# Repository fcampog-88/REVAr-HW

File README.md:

# REVAr-HW
Rede de monitoramento atmosférico de baixo custo (Hardware)

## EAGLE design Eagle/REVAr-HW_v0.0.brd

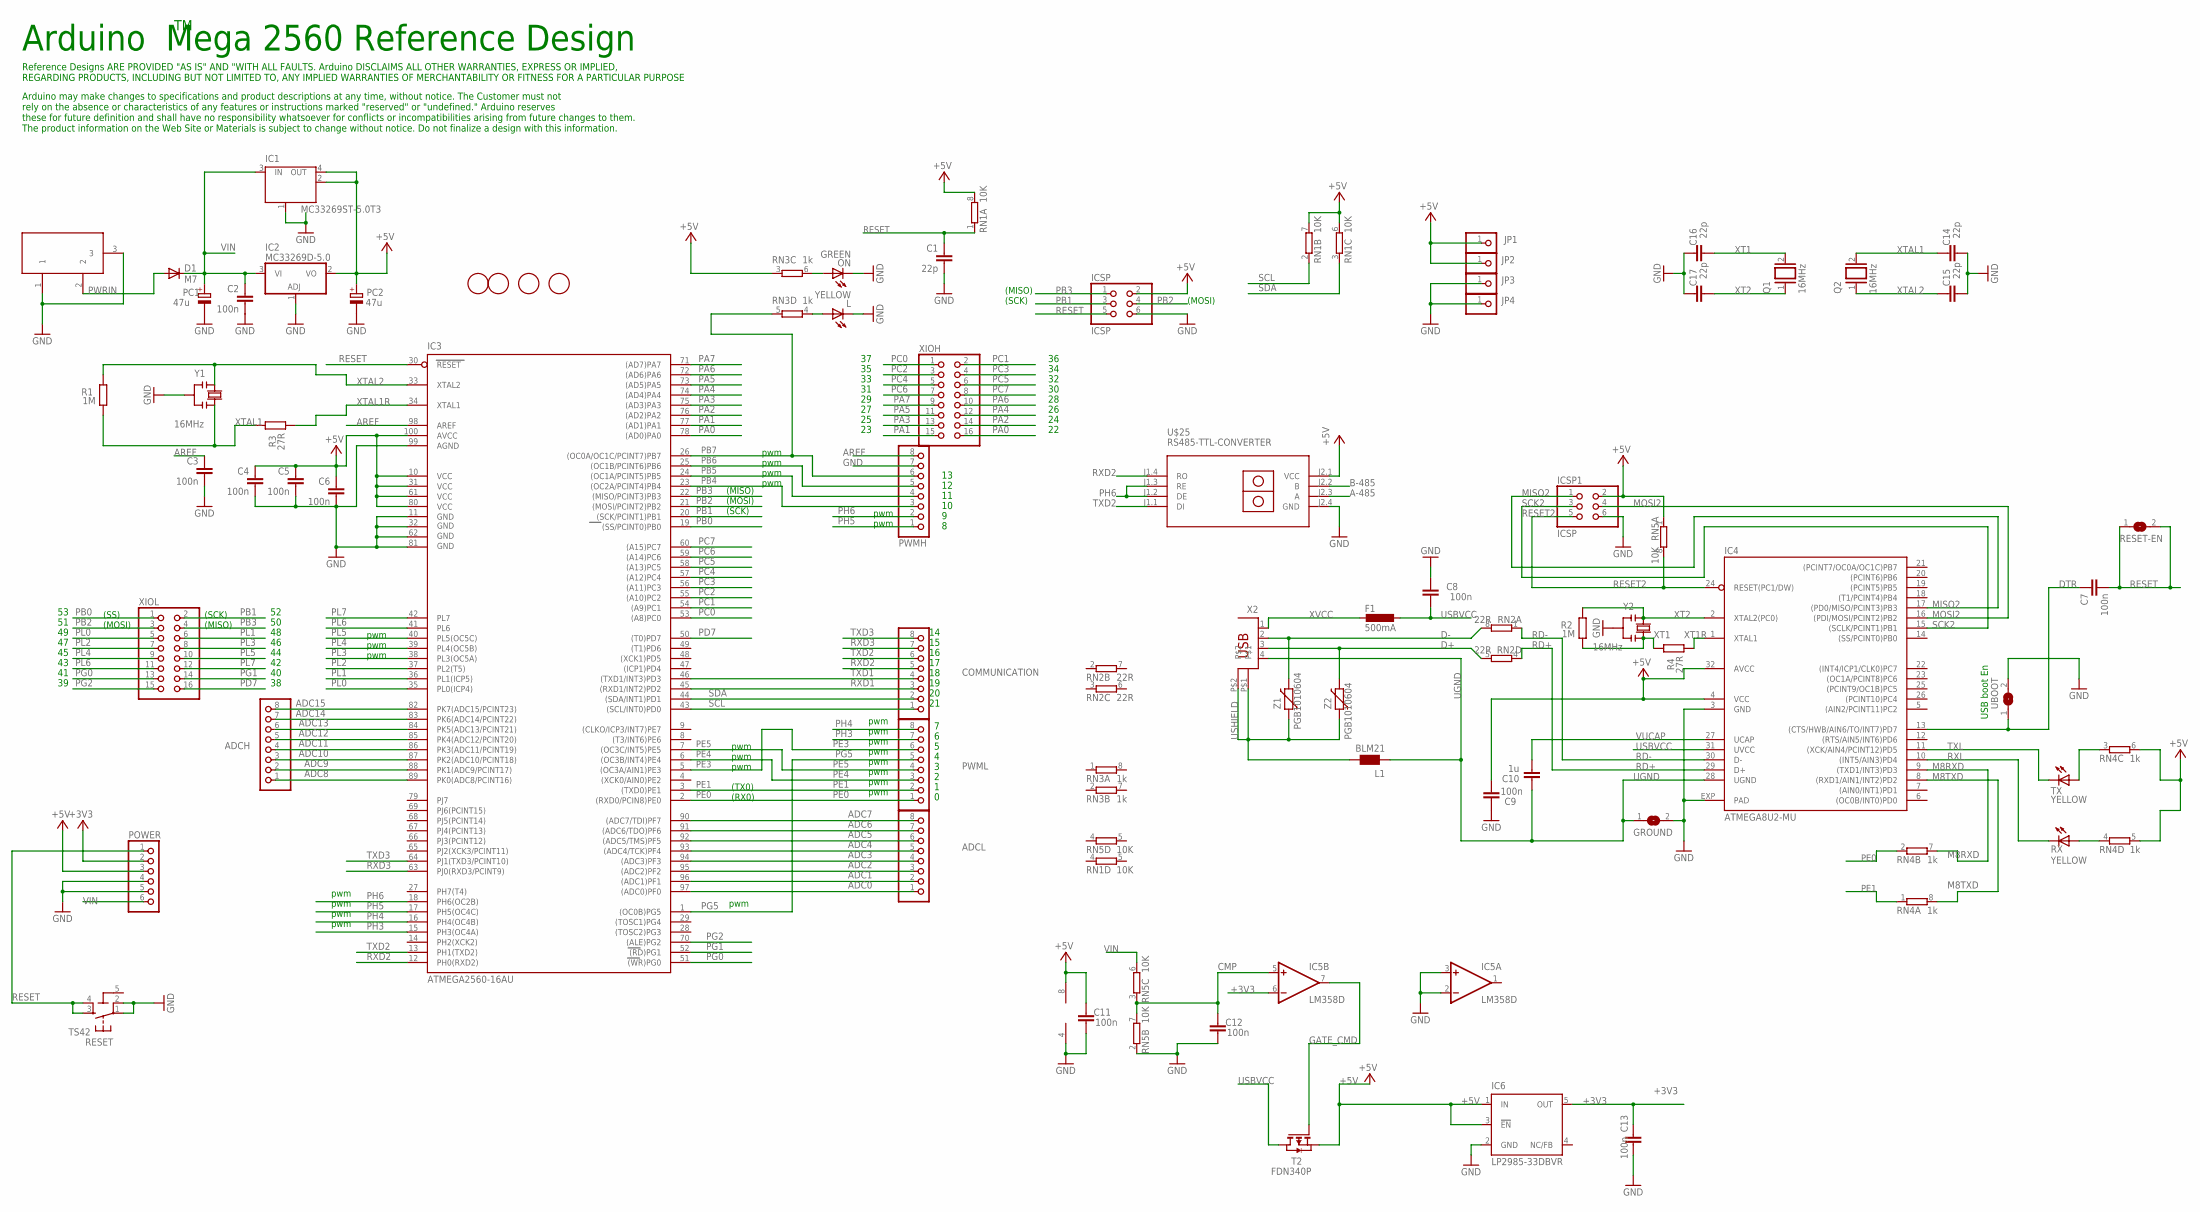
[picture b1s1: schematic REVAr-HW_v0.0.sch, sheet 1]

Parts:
ADCH: PINHD-1X8; 1X08
ADCL: PINHD-1X8; 1X08
C1, C14, C15, C16, C17: 22p; C0603-ROUND
C2, C3, C4, C5, C6, C7, C9, C12, C13: 100n; C0603-ROUND
C8, C11: 100n; C0603
C10: 1u; C0603-ROUND
COMMUNICATION: PINHD-1X8; 1X08
D1: M7; SMB
F1: 500mA; L1812
GROUND: SJ
IC1: MC33269ST-5.0T3; SOT223
IC2: MC33269D-5.0; DPACK
IC3: ATMEGA2560-16AU; TQFP100
IC4: ATMEGA8U2-MU; QFN32
IC5: LM358D; SO08
IC6: LP2985-33DBVR; SOT23-DBV
ICSP, ICSP1: ICSP; 2X03
JP1, JP2, JP3, JP4: PINHD-1X1; 1X01
L: YELLOW; CHIP-LED0805
L1: BLM21; 0805
ON: GREEN; CHIP-LED0805
PC1, PC2: 47u; PANASONIC_D
POWER: PINHD-1X6; 1X06
PWMH: PINHD-1X8; 1X08
PWML: PINHD-1X8; 1X08
Q1, Q2: 16MHz; QS
R1, R2: 1M; R0603-ROUND
R3, R4: 27R; R0603-ROUND
RESET: TS42
RESET-EN: SJ
RN1, RN5: 10K; CAT16
RN2: 22R; CAY16
RN3, RN4: 1k; CAY16
RX: YELLOW; CHIP-LED0805
T2: FDN340P; SOT-23
TX: YELLOW; CHIP-LED0805
U$2, U$3, U$4, U$5: FIDUCIALMOUNT; FIDUCIA-MOUNT
U$25: RS485-TTL-CONVERTER
UBOOT: SJ
X1: DC21MMX; DC-21MM
X2: PN61729
XIOH: PINHD-2X8; 2X08
XIOL: PINHD-2X8; 2X08
Y1, Y2: 16MHz; RESONATOR
Z1, Z2: PGB1010604; CT/CN0603

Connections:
5-GND: RESET.5 (5-GND)
+3V3: C13.2, IC5.6 (-IN), IC6.5 (OUT), POWER.2
+5V: C4.1, C5.1, C6.1, C9.1, C11.2, IC1.2 (OUT), IC1.4 (OUT), IC2.2 (VO), IC3.10 (VCC), IC3.31 (VCC1), IC3.61 (VCC2), IC3.80 (VCC3), IC3.100 (AVCC), IC4.4 (VCC), IC4.32 (AVCC), IC5.8 (V+), IC6.1 (IN), IC6.3 (!EN), ICSP.2, ICSP1.2, JP1.1, JP2.1, PC2.+, POWER.3, RN1.6 (2), RN1.7 (2), RN1.8 (2), RN3.3 (1), RN4.5 (2), RN4.6 (2), RN5.1, T2.2 (S); also elsewhere on the board
A-485: U$25.J2.3 (A); also elsewhere on the board
ADC0: ADCL.1, IC3.97 ((ADC0)PF0)
ADC1: ADCL.2, IC3.96 ((ADC1)PF1)
ADC2: ADCL.3, IC3.95 ((ADC2)PF2)
ADC3: ADCL.4, IC3.94 ((ADC3)PF3)
ADC4: ADCL.5, IC3.93 ((ADC4/TCK)PF4)
ADC5: ADCL.6, IC3.92 ((ADC5/TMS)PF5)
ADC6: ADCL.7, IC3.91 ((ADC6/TDO)PF6)
ADC7: ADCL.8, IC3.90 ((ADC7/TDI)PF7)
ADC8: ADCH.1, IC3.89 (PK0(ADC8/PCINT16))
ADC9: ADCH.2, IC3.88 (PK1(ADC9/PCINT17))
ADC10: ADCH.3, IC3.87 (PK2(ADC10/PCINT18))
ADC11: ADCH.4, IC3.86 (PK3(ADC11/PCINT19))
ADC12: ADCH.5, IC3.85 (PK4(ADC12/PCINT20))
ADC13: ADCH.6, IC3.84 (PK5(ADC13/PCINT21))
ADC14: ADCH.7, IC3.83 (PK6(ADC14/PCINT22))
ADC15: ADCH.8, IC3.82 (PK7(ADC15/PCINT23))
AREF: C3.1, IC3.98 (AREF), PWMH.8
B-485: U$25.J2.2 (B); also elsewhere on the board
CMP: C12.2, IC5.5 (+IN), RN5.3 (1), RN5.7 (2)
D+: RN2.5 (2), X2.3, Z2.2
D-: RN2.8 (2), X2.2, Z1.2
DTR: C7.1, IC4.13 ((CTS/HWB/AIN6/TO/INT7)PD7), UBOOT.1
GATE_CMD: IC5.7 (OUT), T2.3 (G)
GND: C1.2, C2.2, C3.2, C4.2, C5.2, C6.2, C8.2, C9.2, C11.1, C12.1, C13.1, C14.1, C15.1, C16.2, C17.2, GROUND.2, IC1.1 (GND/ADJ), IC2.1 (ADJ), IC3.11 (GND), IC3.32 (GND1), IC3.62 (GND2), IC3.81 (GND3), IC3.99 (AGND), IC4.3 (GND), IC4.EXP (PAD), IC5.2 (-IN), IC5.3 (+IN), IC5.4 (V-), IC6.2 (GND), ICSP.6, ICSP1.6, JP3.1, JP4.1, L.C, ON.C, PC1.-, PC2.-, POWER.4, POWER.5, PWMH.7, RESET.1, RESET.2, RN5.2 (1), U$25.J2.4 (GND), UBOOT.2, X1.1, X1.3, Y1.2, Y2.2; also elsewhere on the board
M8RXD: IC4.9 ((TXD1/INT3)PD3), RN4.7 (2)
M8TXD: IC4.8 ((RXD1/AIN1/INT2)PD2), RN4.8 (2)
MISO2: IC4.17 ((PD0/MISO/PCINT3)PB3), ICSP1.1
MOSI2: IC4.16 ((PDI/MOSI/PCINT2)PB2), ICSP1.4
unnamed: L.A, RN3.4 (1)
unnamed: ON.A, RN3.6 (2)
unnamed: RN4.4 (1), RX.A
unnamed: RN4.3 (1), TX.A
PA0: IC3.78 ((AD0)PA0), XIOH.16
PA1: IC3.77 ((AD1)PA1), XIOH.15
PA2: IC3.76 ((AD2)PA2), XIOH.14
PA3: IC3.75 ((AD3)PA3), XIOH.13
PA4: IC3.74 ((AD4)PA4), XIOH.12
PA5: IC3.73 ((AD5)PA5), XIOH.11
PA6: IC3.72 ((AD6)PA6), XIOH.10
PA7: IC3.71 ((AD7)PA7), XIOH.9
PB0: IC3.19 ((SS/PCINT0)PB0), XIOL.1
PB1: IC3.20 ((SCK/PCINT1)PB1), ICSP.3, XIOL.2; also elsewhere on the board
PB2: IC3.21 ((MOSI/PCINT2)PB2), ICSP.4, XIOL.3; also elsewhere on the board
PB3: IC3.22 ((MISO/PCINT3)PB3), ICSP.1, XIOL.4; also elsewhere on the board
PB4: IC3.23 ((OC2A/PCINT4)PB4), PWMH.3; also elsewhere on the board
PB5: IC3.24 ((OC1A/PCINT5)PB5), PWMH.4; also elsewhere on the board
PB6: IC3.25 ((OC1B/PCINT6)PB6), PWMH.5; also elsewhere on the board
PB7: IC3.26 ((OC0A/OC1C/PCINT7)PB7), PWMH.6, RN3.5 (2); also elsewhere on the board
PC0: IC3.53 ((A8)PC0), XIOH.1
PC1: IC3.54 ((A9)PC1), XIOH.2
PC2: IC3.55 ((A10)PC2), XIOH.3
PC3: IC3.56 ((A11)PC3), XIOH.4
PC4: IC3.57 ((A12)PC4), XIOH.5
PC5: IC3.58 ((A13)PC5), XIOH.6
PC6: IC3.59 ((A14)PC6), XIOH.7
PC7: IC3.60 ((A15)PC7), XIOH.8
PD7: IC3.50 ((T0)PD7), XIOL.16
PE0: IC3.2 ((RXD0/PCIN8)PE0), PWML.1, RN4.2 (1)
PE1: IC3.3 ((TXD0)PE1), PWML.2, RN4.1
PE3: IC3.5 ((OC3A/AIN1)PE3), PWML.6; also elsewhere on the board
PE4: IC3.6 ((OC3B/INT4)PE4), PWML.3; also elsewhere on the board
PE5: IC3.7 ((OC3C/INT5)PE5), PWML.4; also elsewhere on the board
PG0: IC3.51 ((WR)PG0), XIOL.13
PG1: IC3.52 ((RD)PG1), XIOL.14
PG2: IC3.70 ((ALE)PG2), XIOL.15
PG5: IC3.1 ((OC0B)PG5), PWML.5; also elsewhere on the board
PH3: IC3.15 (PH3(OC4A)), PWML.7; also elsewhere on the board
PH4: IC3.16 (PH4(OC4B)), PWML.8; also elsewhere on the board
PH5: IC3.17 (PH5(OC4C)), PWMH.1; also elsewhere on the board
PH6: IC3.18 (PH6(OC2B)), PWMH.2, U$25.J1.2 (DE), U$25.J1.3 (RE)
PL0: IC3.35 (PL0(ICP4)), XIOL.5
PL1: IC3.36 (PL1(ICP5)), XIOL.6
PL2: IC3.37 (PL2(T5)), XIOL.7
PL3: IC3.38 (PL3(OC5A)), XIOL.8
PL4: IC3.39 (PL4(OC5B)), XIOL.9
PL5: IC3.40 (PL5(OC5C)), XIOL.10
PL6: IC3.41 (PL6), XIOL.11
PL7: IC3.42 (PL7), XIOL.12
PWRIN: D1.A, X1.2
RD+: IC4.29 (D+), RN2.4 (1)
RD-: IC4.30 (D-), RN2.1
RESET: C1.1, C7.2, IC3.30 (RESET), ICSP.5, POWER.1, RESET.3, RESET.4, RESET-EN.1, RESET-EN.2, RN1.1
RESET2: IC4.24 (RESET(PC1/DW)), ICSP1.5, RN5.8 (2)
RXD1: COMMUNICATION.3, IC3.45 ((RXD1/INT2)PD2); also elsewhere on the board
RXD2: COMMUNICATION.5, IC3.12 (PH0(RXD2)), U$25.J1.4 (RO)
RXD3: COMMUNICATION.7, IC3.63 (PJ0(RXD3/PCINT9))
RXL: IC4.10 ((INT5/AIN3)PD4), RX.C
SCK2: IC4.15 ((SCLK/PCINT1)PB1), ICSP1.3
SCL: COMMUNICATION.1, IC3.43 ((SCL/INT0)PD0), RN1.2 (1); also elsewhere on the board
SDA: COMMUNICATION.2, IC3.44 ((SDA/INT1)PD1), RN1.3 (1); also elsewhere on the board
TXD1: COMMUNICATION.4, IC3.46 ((TXD1/INT3)PD3); also elsewhere on the board
TXD2: COMMUNICATION.6, IC3.13 (PH1(TXD2)), U$25.J1.1 (DI)
TXD3: COMMUNICATION.8, IC3.64 (PJ1(TXD3/PCINT10))
TXL: IC4.11 ((XCK/AIN4/PCINT12)PD5), TX.C
UGND: C10.2, GROUND.1, IC4.28 (UGND), L1.1, X2.4
USBVCC: C8.1, F1.1, IC4.31 (UVCC), T2.1 (D)
USHIELD: L1.2, X2.P$1, X2.P$2, Z1.1, Z2.1
VCC: U$25.J2.1 (VCC); also elsewhere on the board
VIN: C2.1, D1.C, IC1.3 (IN), IC2.3 (VI), PC1.+, POWER.6, RN5.6 (2)
VUCAP: C10.1, IC4.27 (UCAP)
XT1: C16.1, Q1.2, R2.1, R4.2, Y2.3
XT1R: IC4.1 (XTAL1), R4.1
XT2: C17.1, IC4.2 (XTAL2(PC0)), Q1.1, R2.2, Y2.1
XTAL1: C14.2, Q2.2, R1.1, R3.2, Y1.3
XTAL1R: IC3.34 (XTAL1), R3.1
XTAL2: C15.2, IC3.33 (XTAL2), Q2.1, R1.2, Y1.1
XVCC: F1.2, X2.1

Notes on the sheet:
(SCK)
(MISO)
(MOSI)
pwm
(TX0)
(RX0)
(SS)
USB boot En
Arduino Mega 2560 Reference Design
Arduino may make changes to specifications and product descriptions at any time, without notice. The Customer must not rely on the absence or characteristics of any features or instructions marked "reserved" or "undefined." Arduino reserves these for future definition and shall have no responsibili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
Reference Designs ARE PROVIDED "AS IS" AND "WITH ALL FAULTS. Arduino DISCLAIMS ALL OTHER WARRANTIES, EXPRESS OR IMPLIED, REGARDING PRODUCTS, INCLUDING BUT NOT LIMITED TO, ANY IMPLIED WARRANTIES OF MERCHANTABILITY OR FITNESS FOR A PARTICULAR PURPOSE

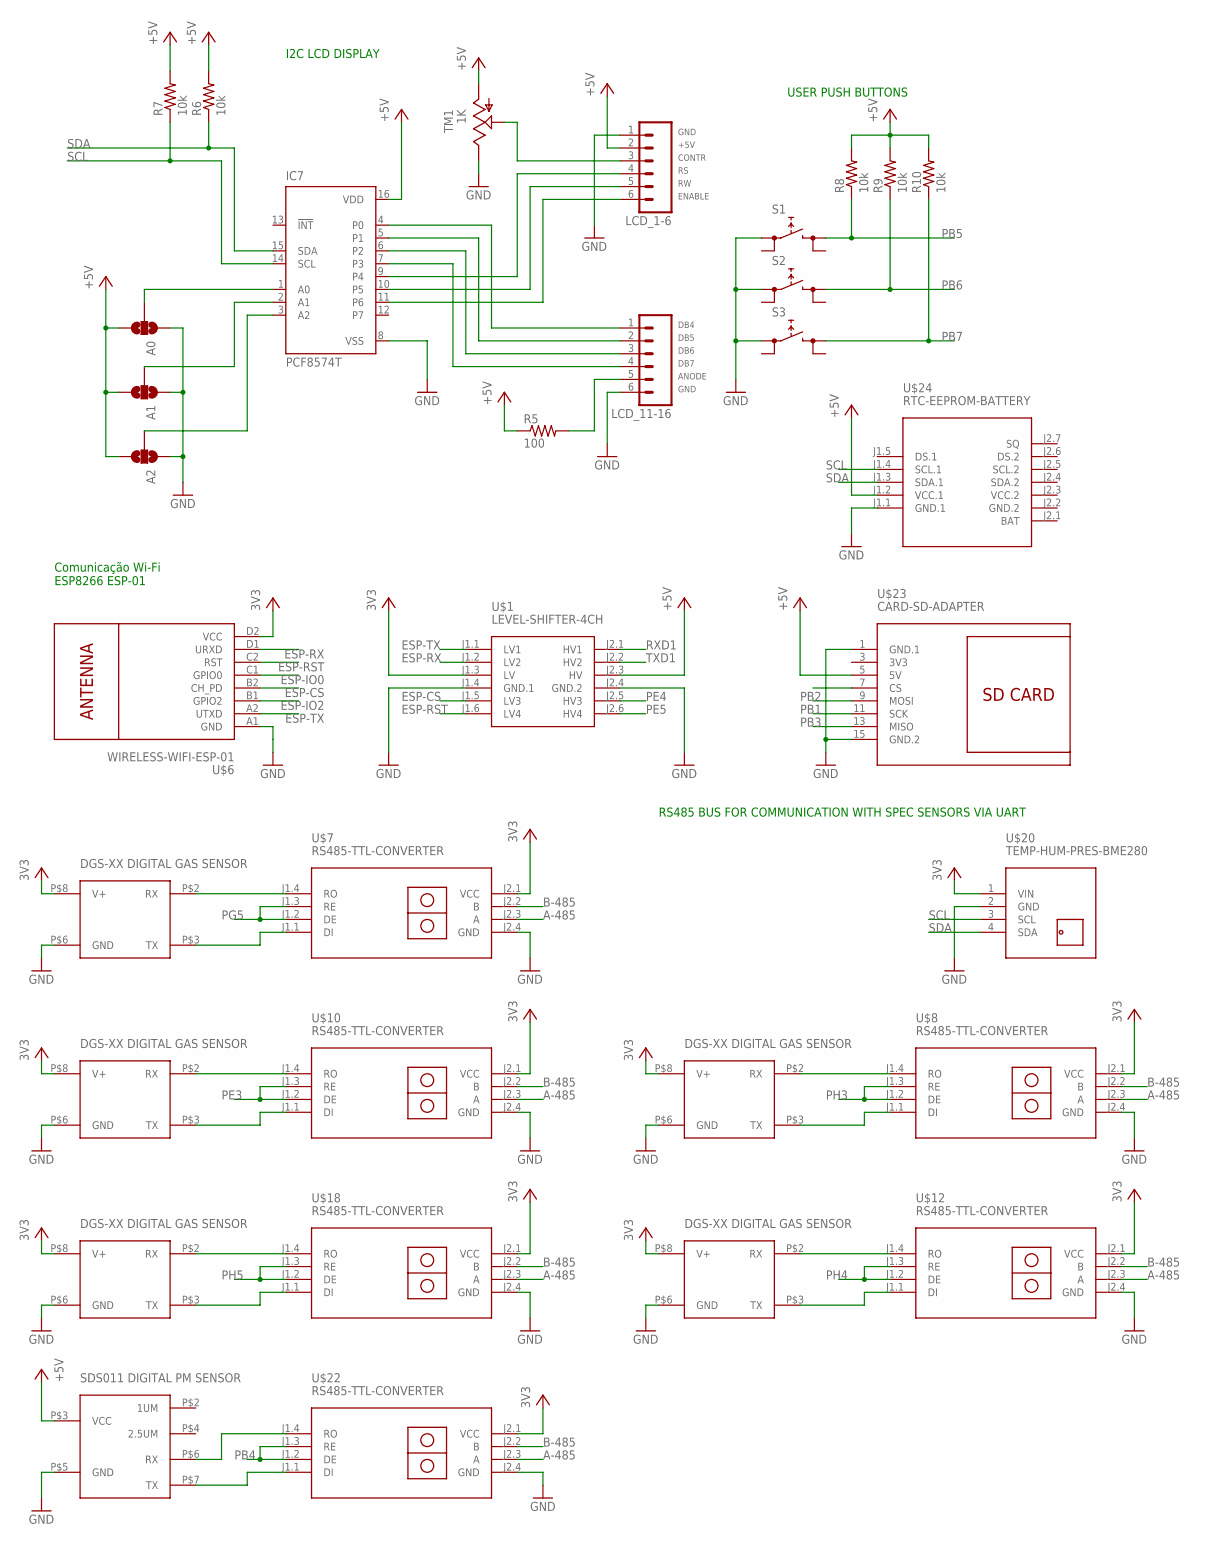
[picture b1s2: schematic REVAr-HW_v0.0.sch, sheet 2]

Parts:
A0, A1, A2: SOLDERJUMPER_2WAYT; SJ_2
IC7: PCF8574T; SO16W
LCD_1-6, LCD_11-16: M06SIP; 1X06
R5: 100; R0805
R6, R7, R8, R9, R10: 10k; R0805
S1, S2, S3: REKN
TM1: 1K; 6MM
U$1: LEVEL-SHIFTER-4CH
U$6: WIRELESS-WIFI-ESP-01
U$7, U$8, U$10, U$12, U$18, U$22: RS485-TTL-CONVERTER
U$9, U$11, U$16, U$17, U$19: DGS-XX
U$20: TEMP-HUM-PRES-BME280
U$21: SDS011
U$23: CARD-SD-ADAPTER
U$24: RTC-EEPROM-BATTERY

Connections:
3V3: U$23.3 (3V3)
+5V: LCD_1-6.2; also elsewhere on the board
A0: A0.2, IC7.1 (A0)
A1: A1.2, IC7.2 (A1)
A2: A2.2, IC7.3 (A2)
A-485: U$7.J2.3 (A), U$8.J2.3 (A), U$10.J2.3 (A), U$12.J2.3 (A), U$18.J2.3 (A), U$22.J2.3 (A); also elsewhere on the board
ANODE: LCD_11-16.5, R5.2
B-485: U$7.J2.2 (B), U$8.J2.2 (B), U$10.J2.2 (B), U$12.J2.2 (B), U$18.J2.2 (B), U$22.J2.2 (B); also elsewhere on the board
CONTR: LCD_1-6.3, TM1.S
DB4: IC7.4 (P0), LCD_11-16.1
DB5: IC7.5 (P1), LCD_11-16.2
DB6: IC7.6 (P2), LCD_11-16.3
DB7: IC7.7 (P3), LCD_11-16.4
ENABLE: IC7.11 (P6), LCD_1-6.6
ESP-CS: U$1.J1.5 (LV3), U$6.B2 (CH_PD)
ESP-IO0: U$6.C1 (GPIO0)
ESP-IO2: U$6.B1 (GPIO2)
ESP-RST: U$1.J1.6 (LV4), U$6.C2 (RST)
ESP-RX: U$1.J1.2 (LV2), U$6.D1 (URXD)
ESP-TX: U$1.J1.1 (LV1), U$6.A2 (UTXD)
GND: A0.1, A1.1, A2.1, IC7.8 (VSS), LCD_1-6.1, LCD_11-16.6, S1.0A (0), S2.0A (0), S3.0A (0), TM1.E, U$1.J1.4 (GND.1), U$1.J2.4 (GND.2), U$6.A1 (GND), U$7.J2.4 (GND), U$8.J2.4 (GND), U$9.P$6 (GND), U$10.J2.4 (GND), U$11.P$6 (GND), U$12.J2.4 (GND), U$16.P$6 (GND), U$17.P$6 (GND), U$18.J2.4 (GND), U$19.P$6 (GND), U$20.2 (GND), U$21.P$5 (GND), U$22.J2.4 (GND), U$23.1 (GND.1), U$23.15 (GND.2), U$24.J1.1 (GND.1); also elsewhere on the board
GND.2: U$24.J2.2 (GND.2)
unnamed: U$7.J1.4 (RO), U$16.P$2 (RX)
unnamed: U$7.J1.1 (DI), U$16.P$3 (TX)
unnamed: U$10.J1.4 (RO), U$11.P$2 (RX)
unnamed: U$10.J1.1 (DI), U$11.P$3 (TX)
unnamed: U$18.J1.4 (RO), U$19.P$2 (RX)
unnamed: U$8.J1.1 (DI), U$9.P$3 (TX)
unnamed: U$18.J1.1 (DI), U$19.P$3 (TX)
unnamed: U$12.J1.4 (RO), U$17.P$2 (RX)
unnamed: U$8.J1.4 (RO), U$9.P$2 (RX)
unnamed: U$12.J1.1 (DI), U$17.P$3 (TX)
unnamed: U$21.P$6 (RX), U$22.J1.4 (RO)
unnamed: U$21.P$7 (TX), U$22.J1.1 (DI)
PB1: U$23.11 (SCK); also elsewhere on the board
PB2: U$23.9 (MOSI); also elsewhere on the board
PB3: U$23.13 (MISO); also elsewhere on the board
PB4: U$22.J1.2 (DE), U$22.J1.3 (RE); also elsewhere on the board
PB5: R8.1, S1.1A (1); also elsewhere on the board
PB6: R9.1, S2.1A (1); also elsewhere on the board
PB7: R10.1, S3.1A (1); also elsewhere on the board
PE3: U$10.J1.2 (DE), U$10.J1.3 (RE); also elsewhere on the board
PE4: U$1.J2.5 (HV3); also elsewhere on the board
PE5: U$1.J2.6 (HV4); also elsewhere on the board
PG5: U$7.J1.2 (DE), U$7.J1.3 (RE); also elsewhere on the board
PH3: U$8.J1.2 (DE), U$8.J1.3 (RE); also elsewhere on the board
PH4: U$12.J1.2 (DE), U$12.J1.3 (RE); also elsewhere on the board
PH5: U$18.J1.2 (DE), U$18.J1.3 (RE); also elsewhere on the board
RS: IC7.9 (P4), LCD_1-6.4
RW: IC7.10 (P5), LCD_1-6.5
RXD1: U$1.J2.1 (HV1); also elsewhere on the board
SCL: IC7.14 (SCL), R7.1, U$20.3 (SCL), U$24.J1.4 (SCL.1); also elsewhere on the board
SDA: IC7.15 (SDA), R6.1, U$20.4 (SDA), U$24.J1.3 (SDA.1); also elsewhere on the board
TXD1: U$1.J2.2 (HV2); also elsewhere on the board
VCC: A0.3, A1.3, A2.3, IC7.16 (VDD), R5.1, R6.2, R7.2, R8.2, R9.2, R10.2, TM1.A, U$1.J1.3 (LV), U$1.J2.3 (HV), U$6.D2 (VCC), U$7.J2.1 (VCC), U$8.J2.1 (VCC), U$9.P$8 (V+), U$10.J2.1 (VCC), U$11.P$8 (V+), U$12.J2.1 (VCC), U$16.P$8 (V+), U$17.P$8 (V+), U$18.J2.1 (VCC), U$19.P$8 (V+), U$20.1 (VIN), U$21.P$3 (VCC), U$22.J2.1 (VCC), U$23.5 (5V), U$24.J1.2 (VCC.1); also elsewhere on the board
VCC.2: U$24.J2.3 (VCC.2)

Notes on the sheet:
Comunicação Wi-Fi ESP8266 ESP-01
RS485 BUS FOR COMMUNICATION WITH SPEC SENSORS VIA UART
I2C LCD DISPLAY
USER PUSH BUTTONS

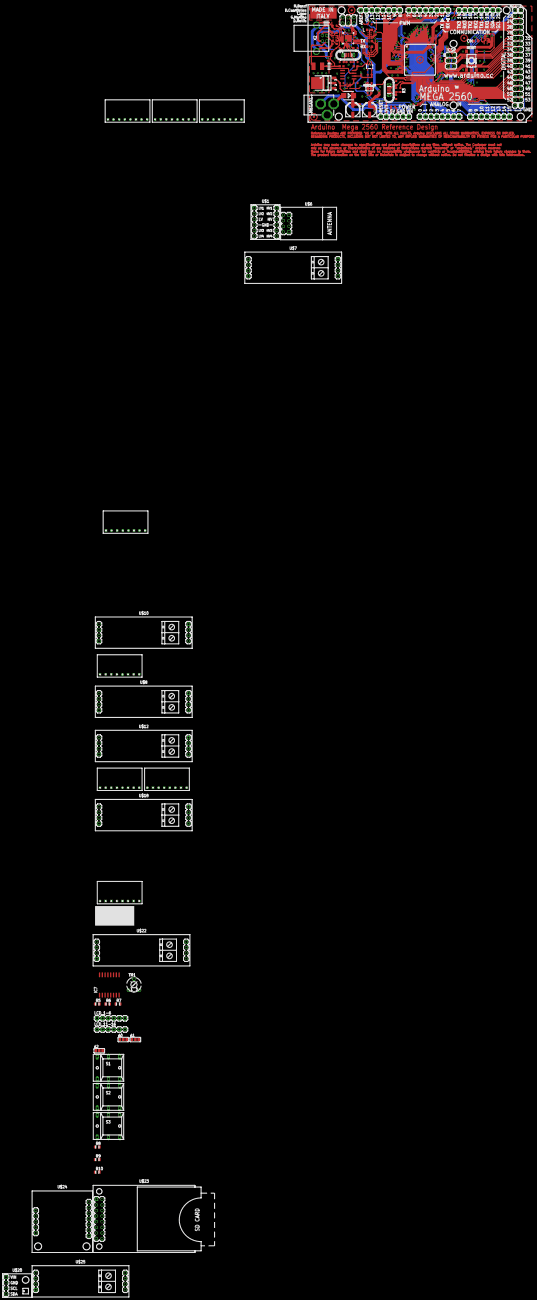
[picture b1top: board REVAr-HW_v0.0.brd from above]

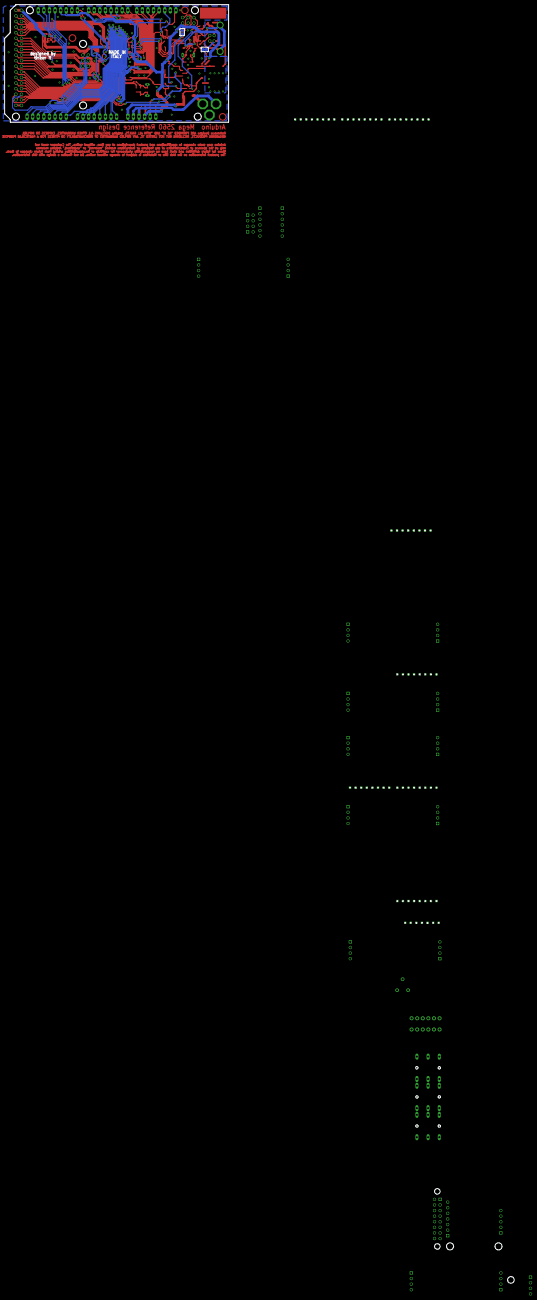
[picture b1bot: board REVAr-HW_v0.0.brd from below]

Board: 2 copper layers, 101.6 x 53.3 mm, 109 parts (2 on the bottom side), 138 nets.

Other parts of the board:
U$13, U$14, U$15: DGS-XX

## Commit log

2018-07-19 [HW] Add Schematic to Repo
2018-07-19 Add Office extensions to gitignore
2018-07-19 [DOC] Add Arduino and ATMEGA 2560 documentation
2018-07-19 [LIB] Add diy-modules Eagle libraries for ESP2866
2018-07-19 [DOC] Add several datasheets
2018-07-24 [DOC] Add new datasheets and update the project information
2018-07-24 [HW] Add SPEC gas sensors and communication via RS485 with Arduino
2018-07-24 Move libraries to newly dedicated Repa
2018-07-25 [DOC] Add SDS011 Datasheet
2018-07-25 [DOC] Add I2C port expander PCF8574 datasheet
2018-07-25 [DOC] Update UART gas and PM sensors mapping info
2018-07-25 [HW] Add PM UART sensor SDS011 to design
2018-07-28 [HW] Add PCF8574 I2C port expander for LCD Display
2018-07-28 [DOC] Update Digital IO with I2C port expander
2018-07-28 [HW] Add push buttons for user interface
2018-07-28 [HW] Add SD Card Adapter
2018-07-28 [DOC] Add SPI pins to Arduino pinout
2018-07-29 [DOC] Add DS1307 and BMP280 datasheets
2018-07-29 [HW] Add BMP280 and DS1307 to design
2018-07-29 [DOC] Add sensors power specifications
2018-07-30 [DOC] Add 3V3 RS485 transceivers datasheets
2018-07-30 [DOC] Add power consumption calculation for Sensors and WiFi
2018-07-30 [DOC] Add HW Diagram as well as I2C and SPI components
2018-08-01 [DOC] Add BS138 Datasheet
2018-08-01 [DOC] Add BOM for buy materials and HW diagram
2018-08-02 [DOC] Add datasheets of relays and DS3231
2018-08-02 [DOC] Update BOM and IO-MAP with relays and RTC
2018-08-21 [DOC] Add new sensors
2018-08-21 [DOC] Add New SGX Sensor

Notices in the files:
parts and their libraries:
diy-modules: Released under the Creative Commons Attribution 4.0 International License: http://creativecommons.org/licenses/by/4.0
SparkFun-Connectors: Licensing: CC v3.0 Share-Alike You are welcome to use this library for commercial purposes.
